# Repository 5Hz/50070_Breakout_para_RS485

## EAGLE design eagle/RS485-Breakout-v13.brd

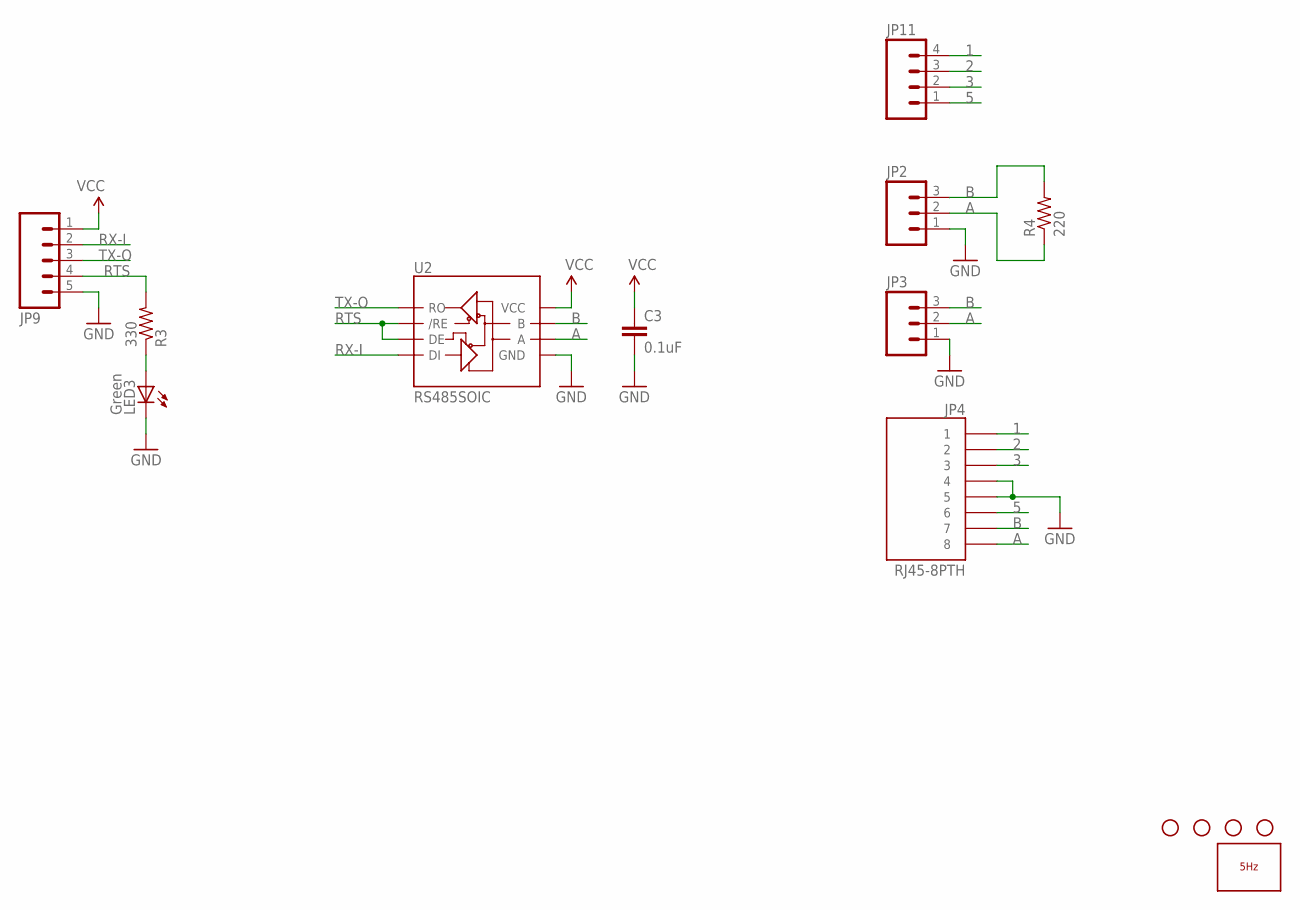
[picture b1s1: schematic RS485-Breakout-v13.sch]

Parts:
C3: 0.1uF; 0402-CAP
JP1, JP6, JP7, JP8: STAND-OFF
JP2: M03SCREW; SCREWTERMINAL-3.5MM-3
JP3: M03PTH; 1X03
JP4: RJ45-8PTH; RJ45-8
JP9: M05PTH; 1X05
JP11: M04PTH; 1X04
LED3: Green; LED-0603
LOGO1: LOGO_5HZ_CIRC_3.5MM; 5HZ_LOGO_CIRC_3.5MM
R3: 330; 0402-RES
R4: 220; 0402-RES
U2: RS485SOIC; SO08

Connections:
1: JP4.1, JP11.4
2: JP4.2, JP11.3
3: JP4.3, JP11.2
5: JP4.6, JP11.1
A: JP2.2, JP3.2, JP4.8, R4.1, U2.6 (A)
B: JP2.3, JP3.3, JP4.7, R4.2, U2.7 (B)
GND: C3.2, JP2.1, JP3.1, JP4.4, JP4.5, JP9.5, LED3.C, U2.5 (GND)
unnamed: LED3.A, R3.1
RTS: JP9.4, R3.2, U2.2 (/RE), U2.3 (DE)
RX-I: JP9.2, U2.4 (DI)
TX-O: JP9.3, U2.1 (RO)
VCC: C3.1, JP9.1, U2.8 (VCC)

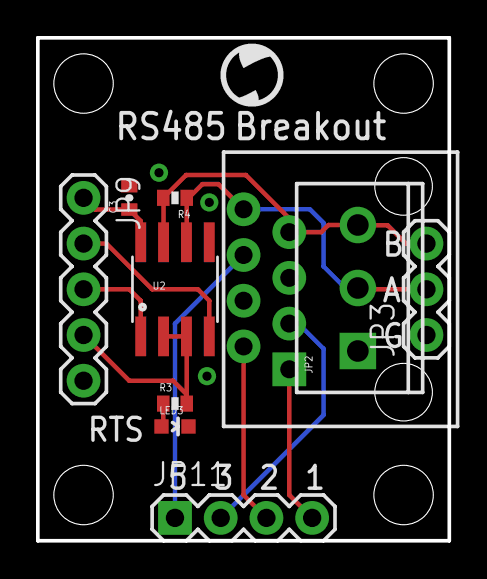
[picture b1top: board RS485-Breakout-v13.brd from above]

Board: 2 copper layers, 22.9 x 27.9 mm, 15 parts (0 on the bottom side), 12 nets.

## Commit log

2014-01-13 creación
